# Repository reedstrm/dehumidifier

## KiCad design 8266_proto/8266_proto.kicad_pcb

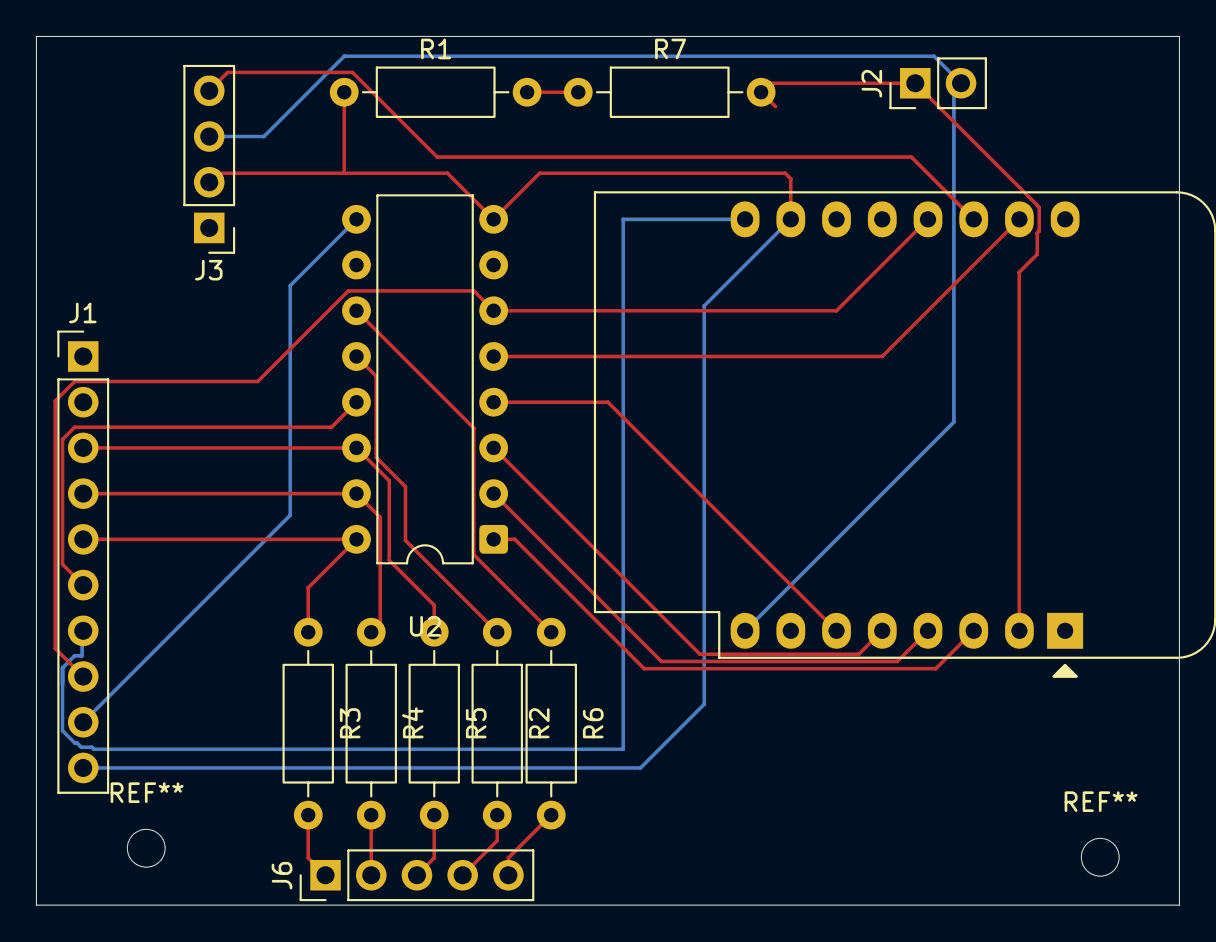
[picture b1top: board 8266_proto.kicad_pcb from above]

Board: 2 copper layers, 63.5 x 48.3 mm, 13 parts (0 on the bottom side), 24 nets.

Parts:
J1: To Power and Relay Board; PinHeader_1x10_P2.54mm_Vertical
J2: EVAP_TEMP; PinHeader_1x02_P2.54mm_Vertical
J3: INTAKE_HUM_TEMP; PinHeader_1x04_P2.54mm_Vertical
J6: LEDs; PinHeader_1x05_P2.54mm_Vertical
R1, R7: 10k; R_Axial_DIN0207_L6.3mm_D2.5mm_P10.16mm_Horizontal
R2, R3, R4, R5, R6: 1K; R_Axial_DIN0207_L6.3mm_D2.5mm_P10.16mm_Horizontal
U1: WEMOS_D1_mini; WEMOS_D1_mini_light
U2: ULN2003A; DIP-16_W7.62mm

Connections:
+3.3V: J2.2, J3.3, U1.8 (3V3)
+5V: J1.7, U1.9 (5V)
/12V: J1.9, U2.9 (COM)
/Bucket Full: J6.5, R6.2
/COMP: J1.6, U2.13 (O4)
/COMP_CMD: U1.6 (MOSI/D7), U2.4 (I4)
/Dehum Req: J6.4, R2.2
/FAN_H: J1.5, R3.1, U2.16 (O1)
/FAN_H_CMD: U1.3 (D0), U2.1 (I1)
/FAN_L: J1.3, R5.1, U2.14 (O3)
/FAN_L_CMD: U1.5 (MISO/D6), U2.3 (I3)
/FAN_M: J1.4, R4.1, U2.15 (O2)
/FAN_M_CMD: U1.4 (SCK/D5), U2.2 (I2)
/FL1: J1.8, U1.13 (SDA/D2), U2.6 (I6)
/Fan High: J6.1, R3.2
/Fan Low: J6.3, R5.2
/Fan Medium: J6.2, R4.2
/HUM_DATA: J3.4, U1.14 (SCL/D1)
/NTC_R: J2.1, R7.2, U1.2 (A0)
GND: J1.10, J3.2, R1.1, U1.10 (GND), U2.8 (GND)
unnamed: R1.2, R7.1
unnamed: U1.15 (RX), U2.5 (I5)
unnamed: R2.1, U2.12 (O5)
unnamed: R6.1, U2.11 (O6)

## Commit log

2026-01-10 first cut
2026-01-10 make it compile. Set the proper pins. Calibrate NTC
2026-01-11 gotta not leak those secrets!
2026-01-12 persist settings.
2026-01-12 less fan chatter. Lockout countdown status
2026-01-12 add two switches and two LEDs
2026-01-12 put back documenting comments and format for easier reading
2026-02-03 fixup LED outputs
2026-02-03 remove input switches. Move some outputs to as-built
2026-02-07 board images and chip docs
2026-02-07 kicad schematic and board
2026-02-07 remove request light from HA: selector only
2026-02-07 Add fan/compressor safety interlocks
2026-02-07 Refine fan interlock behavior
2026-02-07 Route compressor fan start through apply_fan_mode
2026-02-07 Add fan/compressor safety interlocks (#1)
    * Add fan/compressor safety interlocks
    * Refine fan interlock behavior
    * Route compressor fan start through apply_fan_mode
2026-02-07 Remove KiCad backups
2026-02-07 Clarify idle bucket full state
2026-02-07 Remove KiCad backups (#2)
2026-02-07 Clarify idle bucket full state (#3)
